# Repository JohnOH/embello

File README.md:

Embedded software from JeeLabs
==============================

Quick Links
-----------

* [Home page and docs](http://embello.jeelabs.org/)
* [Forth-based JeeLabs JeeNodes Zero](./explore/1608-forth)

Acknowledgments
---------------

With many thanks for the inspiring discussions and code contributions by:

* James Churchill
* Thorsten von Eicken
* Martyn Judd
* Matthias Koch
* Thomas Lohmüller
* John O'Hare
* Joris Pragt
* Frank (SevenW)
* Matthias Urlichs

-- [jcw](http://jeelabs.org/about/)

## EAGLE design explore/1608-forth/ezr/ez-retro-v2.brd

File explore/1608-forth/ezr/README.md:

## EZ-Retro v2

> For pinouts and code related to the hand-wired EZ-Retro v1, see [this
> snapshot](https://github.com/jeelabs/embello/tree/35cb87499ef61468ee42d1ae6326ffff1cd79f05/explore/1608-forth/ezr).

Pin connections:

    PB0 = eZ80 XIN, pin 86
    PB2 = eZ80 ZDA, pin 69 (w/ 10 kΩ pull-up)
    PB4 = eZ80 ZCL, pin 67 (w/ 10 kΩ pull-up)
    PB8 = eZ80 RESET, pin 55

Serial port:

    PA2 = eZ80 RX0, pin 74
    PA3 = eZ80 TX0, pin 73

External 2048 KB RAM:

    A0..A20 = eZ80 ADDR, pins 1-5/8-13/16-21/24-27
    D0..D7 = eZ80 DATA, pins 39-46
    CEN = eZ80 CS0, pin 33
    OEN = eZ80 RDN, pin 51
    WEN = eZ80 WRN, pin 52

Micro SD card:
 
    PA4 = µSD SSEL (CS)
    PA5 = µSD SCLK (CK)
    PA6 = µSD MISO (DO)
    PA7 = µSD MOSI (DI)

SPI interconnect, eZ80 is master:

    PB10 = eZ80 PB1,  pin 101 (BUSY: STM => eZ80)
    PB12 = eZ80 PB0,  pin 100 (NSS: eZ80 => STM))
           eZ80 SS,   pin 102 (10k pullup)
    PB13 = eZ80 SCK,  pin 103
    PB14 = eZ80 MISO, pin 106
    PB15 = eZ80 MOSI, pin 107

EZ-Retro v2 build, after the [PCB fixes](http://jeelabs.org/article/1717e):

Schematic of the STM32F103 board ([from eBay](http://www.ebay.com/itm/222253881878)):

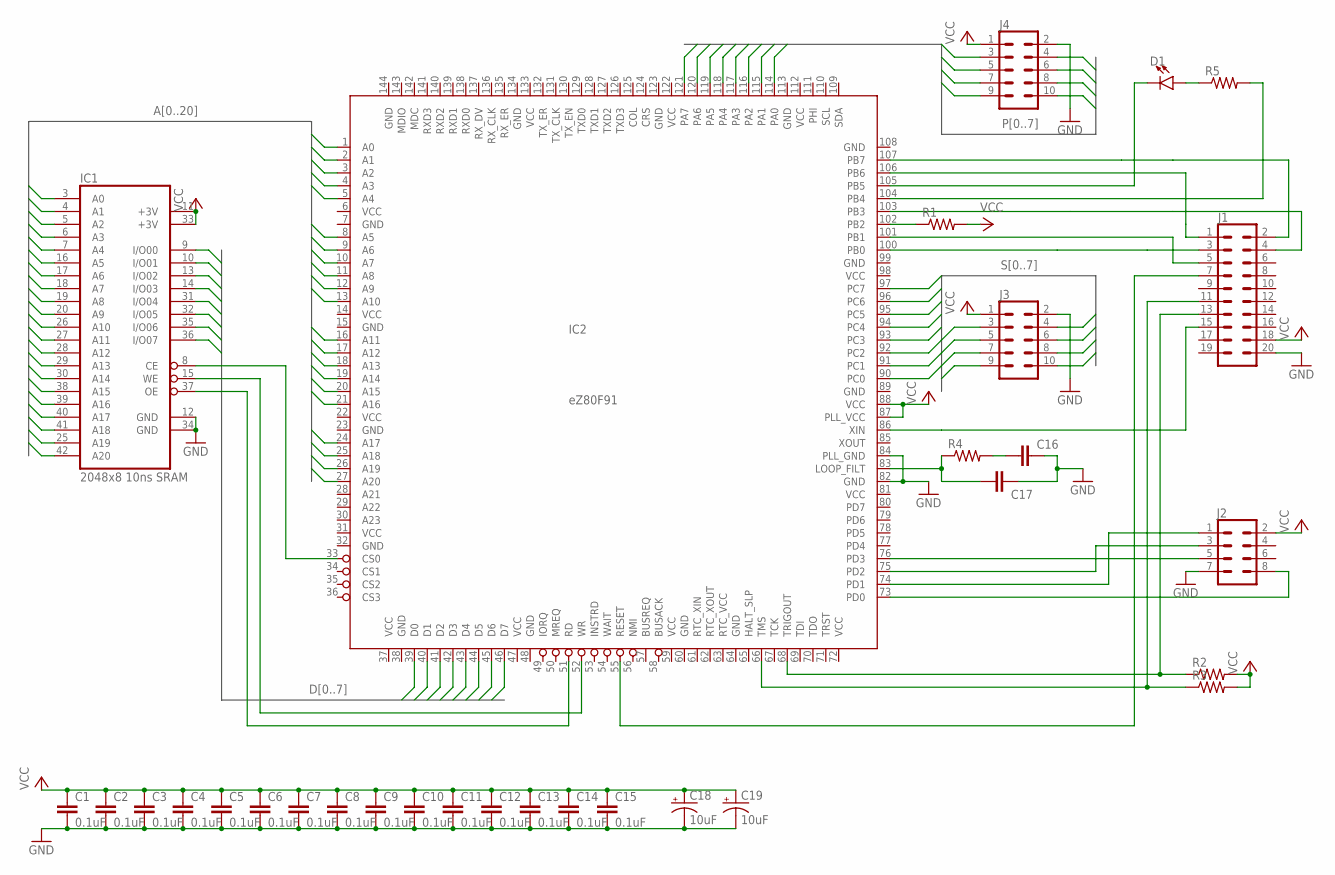
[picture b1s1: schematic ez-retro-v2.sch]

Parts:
C1, C2, C3, C4, C5, C6, C7, C8, C9, C10, C11, C12, C13, C14, C15, C16, C17: 0.1uF; 0603
C18, C19: 10uF; EIA3216
D1: LED1206; LED-1206
IC1: 2048x8 10ns SRAM; TSOPII-Z44
IC2: eZ80F91; TQFP144
J1: CONN_10X2NOSILK; 2X10_NOSILK
J2: CONN_04X2; 2X4
J3, J4: CONN_05X2NO_SILK; 2X5_NOSILK
R1, R2, R3, R4, R5: RESISTOR0603-RES; 0603-RES

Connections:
A0: IC1.3 (A0), IC2.1 (A0)
A1: IC1.4 (A1), IC2.2 (A1)
A2: IC1.5 (A2), IC2.3 (A2)
A3: IC1.6 (A3), IC2.4 (A3)
A4: IC1.7 (A4), IC2.5 (A4)
A5: IC1.16 (A5), IC2.8 (A5)
A6: IC1.17 (A6), IC2.9 (A6)
A7: IC1.18 (A7), IC2.10 (A7)
A8: IC1.19 (A8), IC2.11 (A8)
A9: IC1.20 (A9), IC2.12 (A9)
A10: IC1.26 (A10), IC2.13 (A10)
A11: IC1.27 (A11), IC2.16 (A11)
A12: IC1.28 (A12), IC2.17 (A12)
A13: IC1.29 (A13), IC2.18 (A13)
A14: IC1.30 (A14), IC2.19 (A14)
A15: IC1.38 (A15), IC2.20 (A15)
A16: IC1.39 (A16), IC2.21 (A16)
A17: IC1.40 (A17), IC2.24 (A17)
A18: IC1.41 (A18), IC2.25 (A18)
A19: IC1.25 (A19), IC2.26 (A19)
A20: IC1.42 (A20), IC2.27 (A20)
D0: IC1.9 (I/O00), IC2.39 (D0)
D1: IC1.10 (I/O01), IC2.40 (D1)
D2: IC1.13 (I/O02), IC2.41 (D2)
D3: IC1.14 (I/O03), IC2.42 (D3)
D4: IC1.31 (I/O04), IC2.43 (D4)
D5: IC1.32 (I/O05), IC2.44 (D5)
D6: IC1.35 (I/O06), IC2.45 (D6)
D7: IC1.36 (I/O07), IC2.46 (D7)
GND: C1.2, C2.2, C3.2, C4.2, C5.2, C6.2, C7.2, C8.2, C9.1, C10.2, C11.2, C12.2, C13.2, C14.2, C15.2, C16.2, C17.2, C18.-, C19.-, IC1.12 (GND), IC1.34 (GND), IC2.7 (GND), IC2.15 (GND), IC2.23 (GND), IC2.32 (GND), IC2.38 (GND), IC2.48 (GND), IC2.60 (GND), IC2.64 (GND), IC2.82 (GND), IC2.84 (PLL_GND), IC2.89 (GND), IC2.99 (GND), IC2.108 (GND), IC2.113 (GND), IC2.123 (GND), IC2.134 (GND), J1.20, J2.7, J3.2, J4.2
unnamed: IC1.37 (OE), IC2.51 (RD)
unnamed: IC1.15 (WE), IC2.52 (WR)
unnamed: IC1.8 (CE), IC2.33 (CS0)
unnamed: IC2.100 (PB0), J1.3
unnamed: IC2.106 (PB6), J1.1
unnamed: IC2.103 (PB3), J1.4
unnamed: IC2.107 (PB7), J1.2
unnamed: IC2.86 (XIN), J1.15
unnamed: IC2.55 (RESET), J1.7
unnamed: IC2.101 (PB1), J1.5
unnamed: IC2.66 (TMS), J1.11, R3.1
unnamed: IC2.102 (PB2), R1.1
unnamed: IC2.68 (TRIGOUT), J1.13, R2.1
unnamed: IC2.74 (PD1), J2.1
unnamed: IC2.73 (PD0), J2.8
unnamed: IC2.76 (PD3), J2.5
unnamed: IC2.75 (PD2), J2.3
unnamed: C17.1, IC2.83 (LOOP_FILT), R4.1
unnamed: C16.1, R4.2
unnamed: D1.A, R5.1
unnamed: D1.C, IC2.105 (PB5)
unnamed: IC2.104 (PB4), R5.2
P0: IC2.114 (PA0), J4.3
P1: IC2.115 (PA1), J4.4
P2: IC2.116 (PA2), J4.5
P3: IC2.117 (PA3), J4.6
P4: IC2.118 (PA4), J4.7
P5: IC2.119 (PA5), J4.8
P6: IC2.120 (PA6), J4.9
P7: IC2.121 (PA7), J4.10
RTC_VCC: IC2.63 (RTC_VCC)
S0: IC2.90 (PC0), J3.3
S1: IC2.91 (PC1), J3.4
S2: IC2.92 (PC2), J3.5
S3: IC2.93 (PC3), J3.6
S4: IC2.94 (PC4), J3.7
S5: IC2.95 (PC5), J3.8
S6: IC2.96 (PC6), J3.9
S7: IC2.97 (PC7), J3.10
VCC: C1.1, C2.1, C3.1, C4.1, C5.1, C6.1, C7.1, C8.1, C9.2, C10.1, C11.1, C12.1, C13.1, C14.1, C15.1, C18.+, C19.+, IC1.11 (+3V), IC1.33 (+3V), IC2.6 (VCC), IC2.14 (VCC), IC2.22 (VCC), IC2.31 (VCC), IC2.37 (VCC), IC2.47 (VCC), IC2.59 (VCC), IC2.72 (VCC), IC2.81 (VCC), IC2.87 (PLL_VCC), IC2.88 (VCC), IC2.98 (VCC), IC2.112 (VCC), IC2.122 (VCC), IC2.133 (VCC), J1.18, J2.2, J3.1, J4.1, R1.2, R2.2, R3.2
WP: IC2.144 (WP)

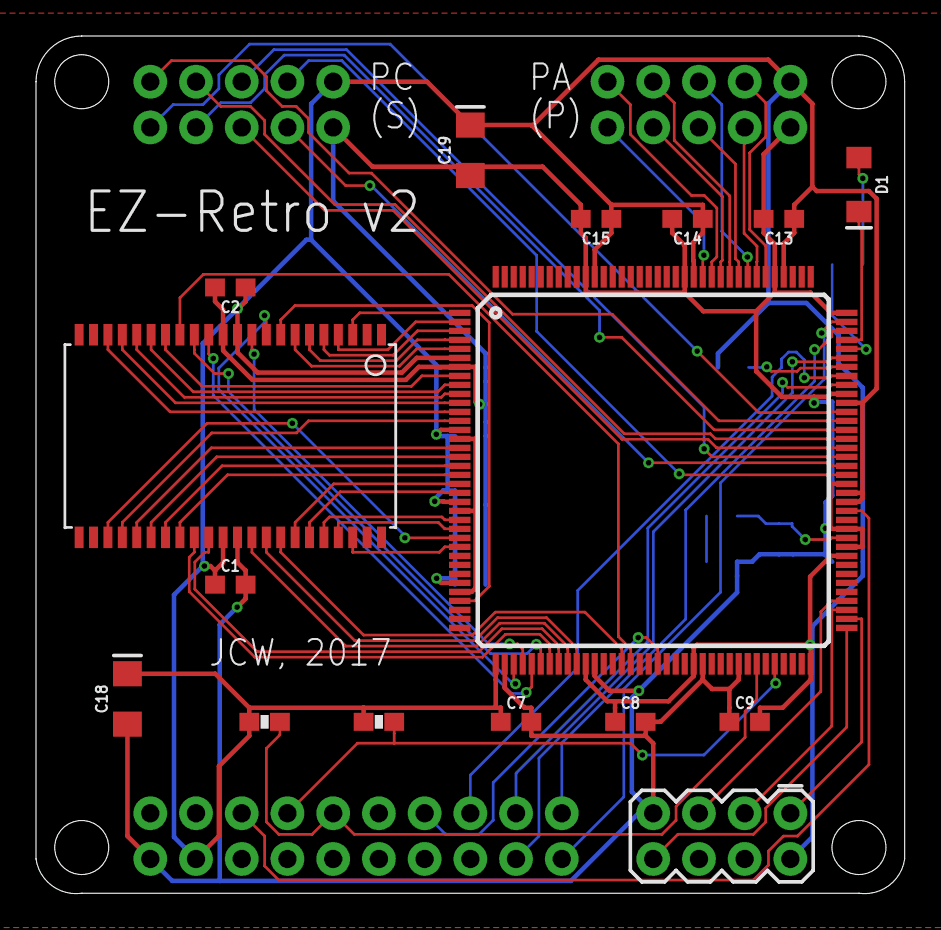
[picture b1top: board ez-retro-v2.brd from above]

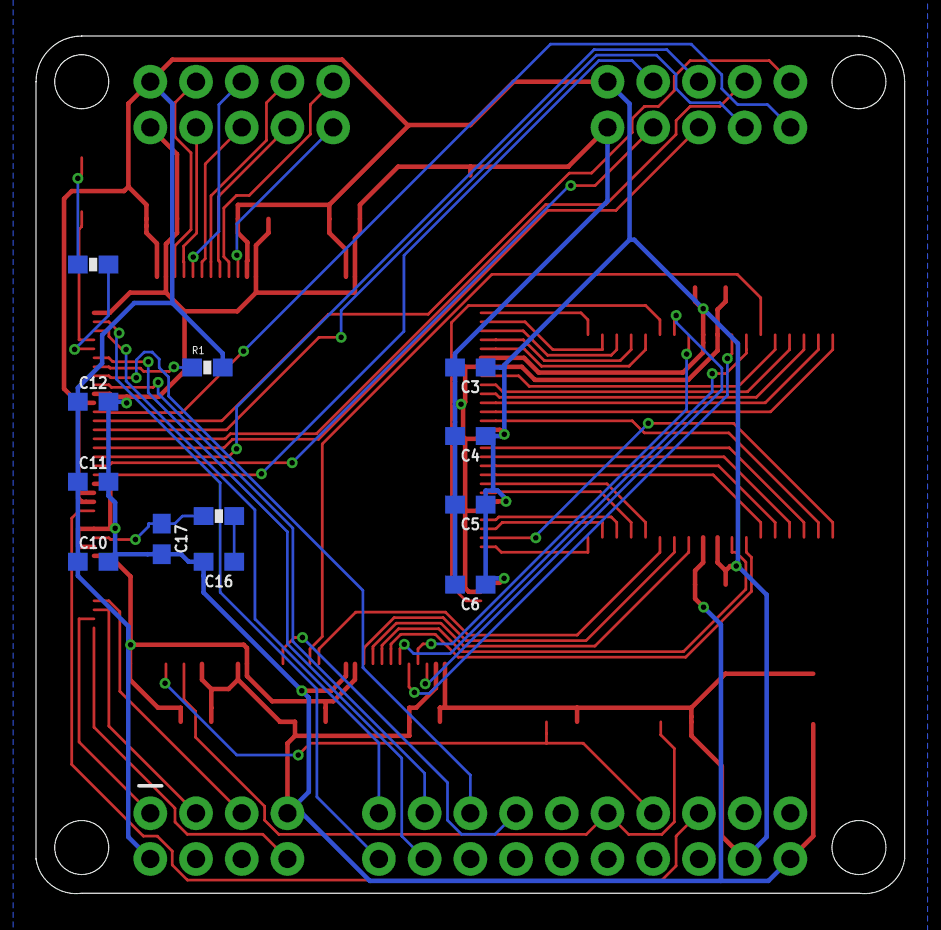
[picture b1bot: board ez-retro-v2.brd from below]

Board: 2 copper layers, 48.3 x 47.6 mm, 31 parts (12 on the bottom side), 69 nets.

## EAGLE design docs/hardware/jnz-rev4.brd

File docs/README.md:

This documentation can be viewed at <http://embello.jeelabs.org>.

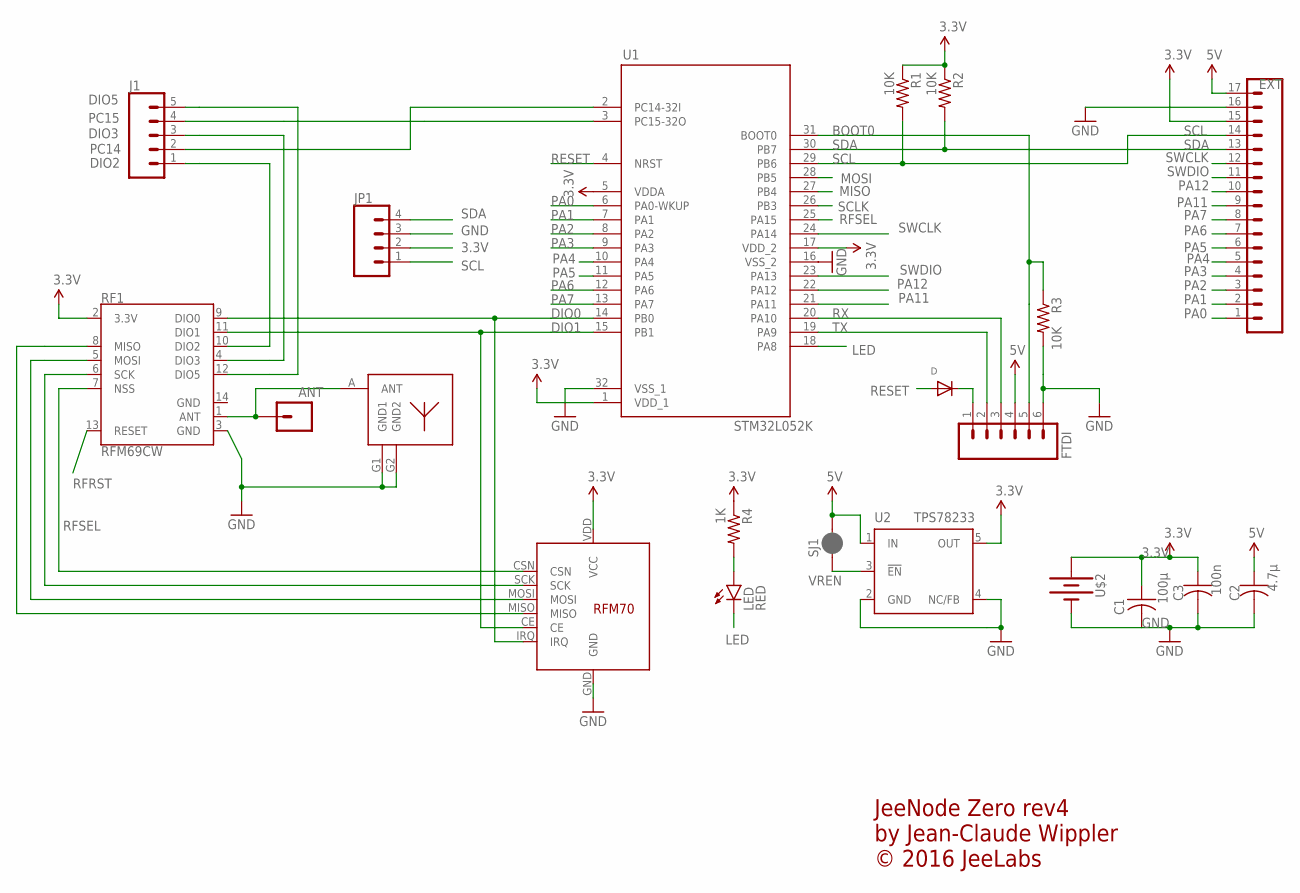
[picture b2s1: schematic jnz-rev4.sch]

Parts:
ANT: CONN_01PTH_NO_SILK_KIT; 1X01NS_KIT
C1: 100µ; C1206
C2: 4.7µ; C0805
C3: 100n; C0603
D: DIODESOD-323F; SOD-323F
EXT: CONN_17NOSILK; 1X17_NO_SILK
FTDI: CONN_06NO_SILK_FEMALE_PTH; 1X06_NO_SILK
J1: CONN_05NO_SILK; 1X05_NO_SILK
JP1: CONN_04SMD_RA_FEMALE; 1X04_SMD_RA_FEMALE
LED: RED; LED-0603
R1, R2, R3: 10K; R0603
R4: 1K; R0603
RF1: RFM69CW; RFM69CW-XXXS2
RF2: RFM75; RFM70
SJ1: JUMPER-SMT_2_NC_PASTE_NO-SILK; SMT-JUMPER_2_NC_PASTE_NO-SILK
U1: STM32L052K; TQFP32-08
U2: TPS78233; SOT23-DBV
U$1: UFL
U$2: BATTERY-20MM_SMD_4LEGS; BATTCON_20MM_4LEGS

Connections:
3.3V: C1.1, C3.1, EXT.15, JP1.2, R1.1, R2.1, R4.1, RF1.2 (3.3V), RF2.VDD (VCC), U1.1 (VDD_1), U1.5 (VDDA), U1.17 (VDD_2), U2.5 (OUT), U$2.POSITIVE@1 (+), U$2.POSITIVE@2 (+), U$2.POSITIVE@3 (+), U$2.POSITIVE@4 (+)
5V: C2.1, EXT.17, FTDI.4, SJ1.2, U2.1 (IN)
BOOT0: FTDI.5, R3.1, U1.31 (BOOT0)
DIO0: RF1.9 (DIO0), RF2.IRQ, U1.14 (PB0)
DIO1: RF1.11 (DIO1), RF2.CE, U1.15 (PB1)
DIO2: J1.1, RF1.10 (DIO2)
DIO3: J1.3, RF1.4 (DIO3)
DIO5: J1.5, RF1.12 (DIO5)
GND: C1.2, C2.2, C3.2, EXT.16, FTDI.6, JP1.3, R3.2, RF1.3 (GND), RF1.14 (GND), RF2.GND, U1.16 (VSS_2), U1.32 (VSS_1), U2.2 (GND), U2.4 (NC/FB), U$1.G1 (GND1), U$1.G2 (GND2), U$2.NEGATIVE (-)
LED: LED.C, U1.18 (PA8)
MISO: RF1.8 (MISO), RF2.MISO, U1.27 (PB4)
MOSI: RF1.5 (MOSI), RF2.MOSI, U1.28 (PB5)
unnamed: D.C, FTDI.1
unnamed: LED.A, R4.2
unnamed: ANT.1, RF1.1 (ANT), U$1.A (ANT)
PA0: EXT.1, U1.6 (PA0-WKUP)
PA1: EXT.2, U1.7 (PA1)
PA2: EXT.3, U1.8 (PA2)
PA3: EXT.4, U1.9 (PA3)
PA4: EXT.5, U1.10 (PA4)
PA5: EXT.6, U1.11 (PA5)
PA6: EXT.7, U1.12 (PA6)
PA7: EXT.8, U1.13 (PA7)
PA11: EXT.9, U1.21 (PA11)
PA12: EXT.10, U1.22 (PA12)
PC14: J1.2, U1.2 (PC14-32I)
PC15: J1.4, U1.3 (PC15-32O)
RESET: D.A, U1.4 (NRST)
RFRST: RF1.13 (RESET)
RFSEL: RF1.7 (NSS), RF2.CSN, U1.25 (PA15)
RX: FTDI.3, U1.20 (PA10)
SCL: EXT.14, JP1.1, R1.2, U1.29 (PB6)
SCLK: RF1.6 (SCK), RF2.SCK, U1.26 (PB3)
SDA: EXT.13, JP1.4, R2.2, U1.30 (PB7)
SWCLK: EXT.12, U1.24 (PA14)
SWDIO: EXT.11, U1.23 (PA13)
TX: FTDI.2, U1.19 (PA9)
VREN: SJ1.1, U2.3 (!EN)

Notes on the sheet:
JeeNode Zero rev4 by Jean-Claude Wippler © 2016 JeeLabs

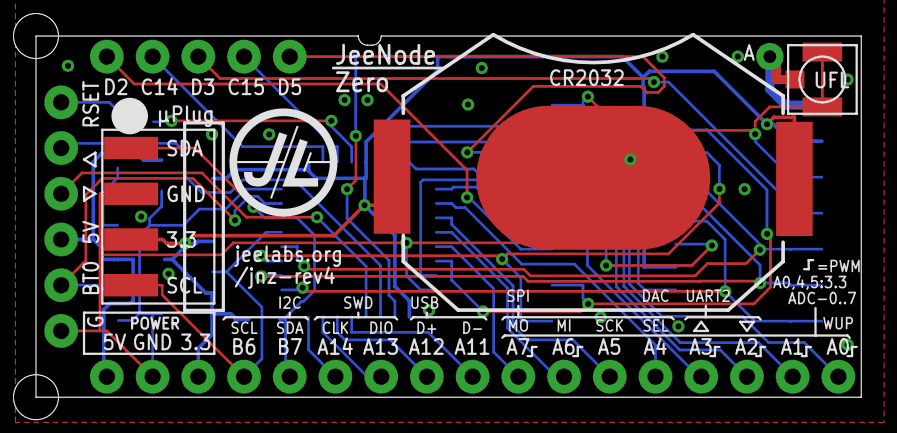
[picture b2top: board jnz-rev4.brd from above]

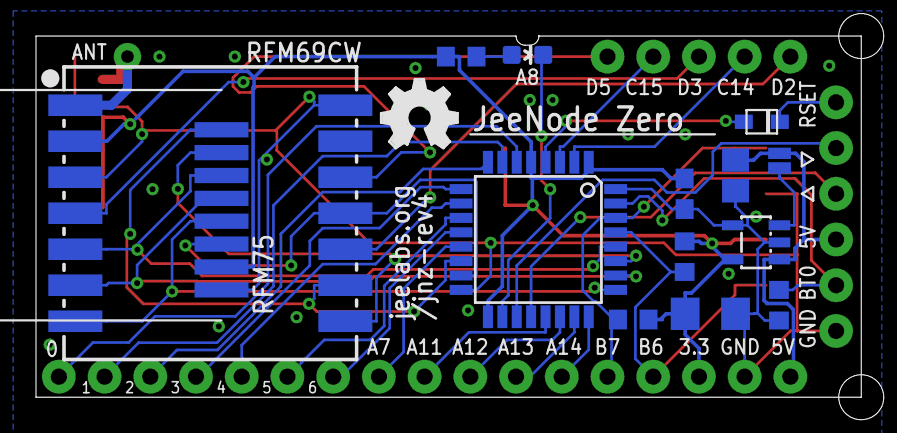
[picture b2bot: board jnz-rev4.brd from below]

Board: 2 copper layers, 45.8 x 20.1 mm, 22 parts (15 on the bottom side), 37 nets.

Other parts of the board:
LOGO1: OSHW_LOGO_FILLX0150-NT; OSHW_FILLX150_NOTEXT

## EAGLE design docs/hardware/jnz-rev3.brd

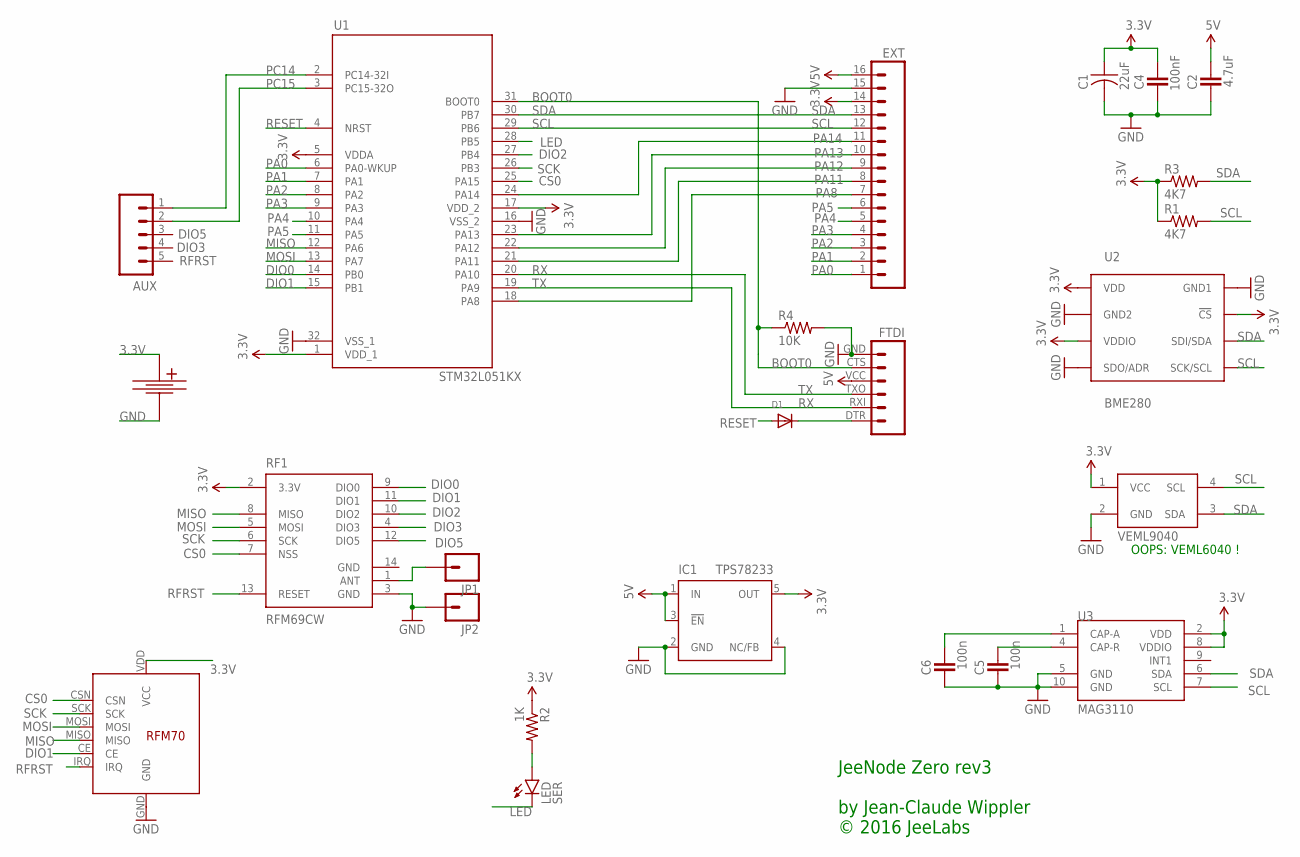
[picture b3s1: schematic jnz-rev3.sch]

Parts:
AUX: M05NO_SILK; 1X05_NO_SILK
C1: 22uF; C0805
C2: 4.7uF; C0805K
C4: 100nF; C0603K
C5, C6: 100n; C0603K
D1: DIODESOD-323F; SOD-323F
EXT: M161X16_NO_SILK; 1X16_NO_SILK
FTDI: FTDI_BASICPTH; FTDI_BASIC
IC1: TPS78233; SOT23-DBV
JP1, JP2: M01NOSILK-KIT; 1X01NS-KIT
LED: SER; LED-0603
R1, R3: 4K7; 0603-RES
R2: 1K; 0603-RES
R4: 10K; 0603-RES
RF1: RFM69CW; RFM69CW-XXXS2
RF2: RFM7x; RFM70
U1: STM32L051KX; TQFP32-08
U2: BME280; BME280_LGA
U3: MAG3110; DFN-10
U$2: CR2032-SMD
U$3: VEML6040; OPLGA-4

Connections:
3.3V: C1.1, C4.1, EXT.14, IC1.5 (OUT), R1.1, R2.1, R3.1, RF1.2 (3.3V), RF2.VDD (VCC), U1.1 (VDD_1), U1.5 (VDDA), U1.17 (VDD_2), U2.P$2 (!CS), U2.P$6 (VDDIO), U2.P$8 (VDD), U3.2 (VDD), U3.8 (VDDIO), U$2.POS (+), U$3.1 (VCC)
5V: C2.1, EXT.16, FTDI.VCC (4), IC1.1 (IN), IC1.3 (!EN)
BOOT0: FTDI.CTS (5), R4.1, U1.31 (BOOT0)
CS0: RF1.7 (NSS), RF2.CSN, U1.25 (PA15)
DIO0: RF1.9 (DIO0), U1.14 (PB0)
DIO1: RF1.11 (DIO1), RF2.CE, U1.15 (PB1)
DIO2: RF1.10 (DIO2), U1.27 (PB4)
DIO3: AUX.4, RF1.4 (DIO3)
DIO5: AUX.3, RF1.12 (DIO5)
GND: C1.2, C2.2, C4.2, C5.2, C6.2, EXT.15, FTDI.GND (6), IC1.2 (GND), IC1.4 (NC/FB), JP2.1, R4.2, RF1.3 (GND), RF1.14 (GND), RF2.GND, U1.16 (VSS_2), U1.32 (VSS_1), U2.P$1 (GND1), U2.P$5 (SDO/ADR), U2.P$7 (GND2), U3.5 (GND), U3.10 (GND), U$2.NEG (-), U$3.2 (GND)
LED: LED.C, U1.28 (PB5)
MISO: RF1.8 (MISO), RF2.MISO, U1.12 (PA6)
MOSI: RF1.5 (MOSI), RF2.MOSI, U1.13 (PA7)
unnamed: D1.C, FTDI.DTR (1)
unnamed: LED.A, R2.2
unnamed: C5.1, U3.4 (CAP-R)
unnamed: C6.1, U3.1 (CAP-A)
unnamed: JP1.1, RF1.1 (ANT)
PA0: EXT.1, U1.6 (PA0-WKUP)
PA1: EXT.2, U1.7 (PA1)
PA2: EXT.3, U1.8 (PA2)
PA3: EXT.4, U1.9 (PA3)
PA4: EXT.5, U1.10 (PA4)
PA5: EXT.6, U1.11 (PA5)
PA8: EXT.7, U1.18 (PA8)
PA11: EXT.8, U1.21 (PA11)
PA12: EXT.9, U1.22 (PA12)
PA13: EXT.10, U1.23 (PA13)
PA14: EXT.11, U1.24 (PA14)
PC14: AUX.1, U1.2 (PC14-32I)
PC15: AUX.2, U1.3 (PC15-32O)
RESET: D1.A, U1.4 (NRST)
RFRST: AUX.5, RF1.13 (RESET), RF2.IRQ
RX: FTDI.TXO (3), U1.20 (PA10)
SCK: RF1.6 (SCK), RF2.SCK, U1.26 (PB3)
SCL: EXT.12, R1.2, U1.29 (PB6), U2.P$4 (SCK/SCL), U3.7 (SCL), U$3.4 (SCL)
SDA: EXT.13, R3.2, U1.30 (PB7), U2.P$3 (SDI/SDA), U3.6 (SDA), U$3.3 (SDA)
TX: FTDI.RXI (2), U1.19 (PA9)

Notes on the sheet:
JeeNode Zero rev3 by Jean-Claude Wippler © 2016 JeeLabs
OOPS: VEML6040 !

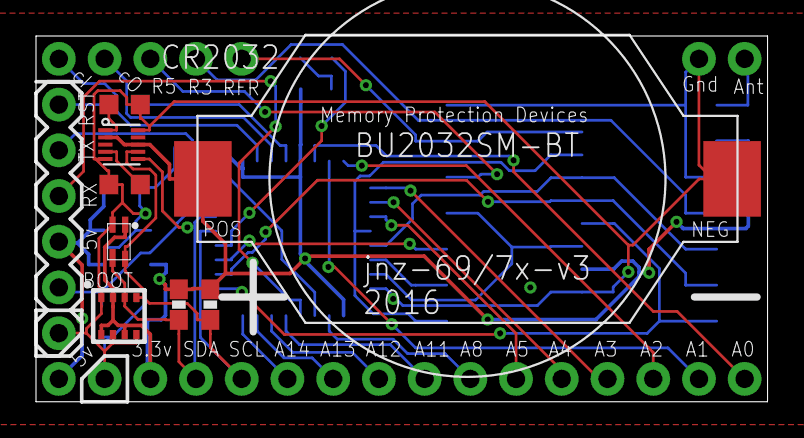
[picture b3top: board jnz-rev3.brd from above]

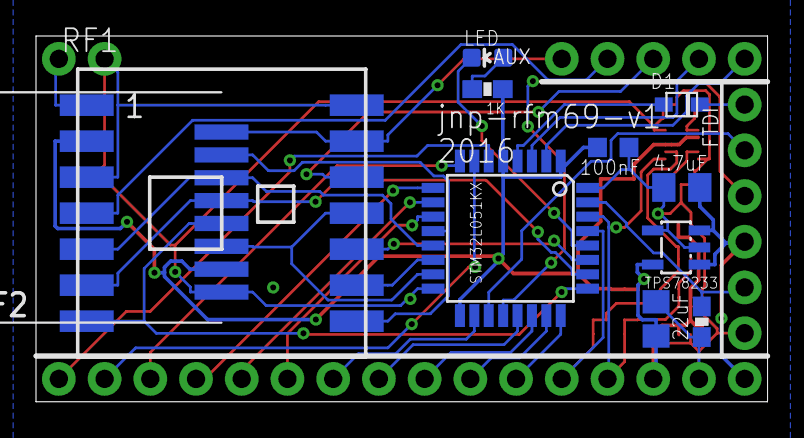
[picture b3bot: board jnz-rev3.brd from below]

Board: 2 copper layers, 40.6 x 20.3 mm, 24 parts (11 on the bottom side), 38 nets.

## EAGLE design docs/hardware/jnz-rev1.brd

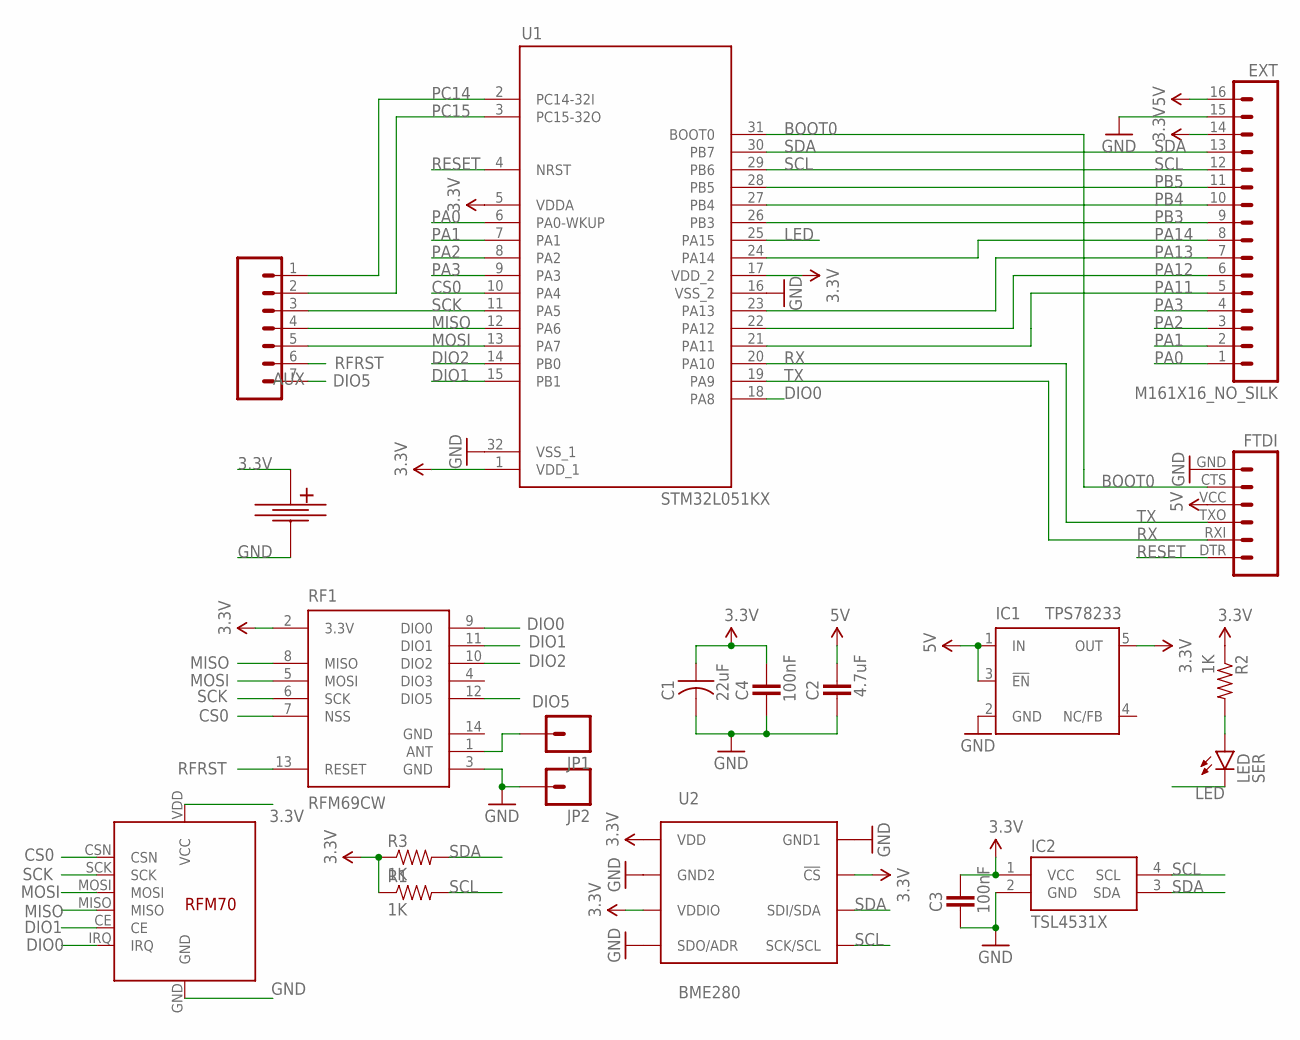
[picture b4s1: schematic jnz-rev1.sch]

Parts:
AUX: M07; 1X07
C1: 22uF; C0805
C2: 4.7uF; C0805K
C3, C4: 100nF; C0603K
EXT: M161X16_NO_SILK; 1X16_NO_SILK
FTDI: FTDI_BASICPTH; FTDI_BASIC
IC1: TPS78233; SOT23-DBV
IC2: TSL4531X; AMS_CL
JP1, JP2: M01NOSILK-KIT; 1X01NS-KIT
LED: SER; LED-0603
R1, R2, R3: 1K; 0603-RES
RF1: RFM69CW; RFM69CW-XXXS2
RF2: RFM7x; RFM70
U1: STM32L051KX; TQFP32-08
U2: BME280; BME280_LGA
U$2: CR2032-SMD

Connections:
3.3V: C1.1, C3.1, C4.1, EXT.14, IC1.5 (OUT), IC2.1 (VCC), R1.1, R2.1, R3.1, RF1.2 (3.3V), RF2.VDD (VCC), U1.1 (VDD_1), U1.5 (VDDA), U1.17 (VDD_2), U2.P$2 (!CS), U2.P$6 (VDDIO), U2.P$8 (VDD), U$2.POS (+)
5V: C2.1, EXT.16, FTDI.VCC (4), IC1.1 (IN), IC1.3 (!EN)
BOOT0: FTDI.CTS (5), U1.31 (BOOT0)
CS0: RF1.7 (NSS), RF2.CSN, U1.10 (PA4)
DIO0: RF1.9 (DIO0), RF2.IRQ, U1.18 (PA8)
DIO1: RF1.11 (DIO1), RF2.CE, U1.15 (PB1)
DIO2: RF1.10 (DIO2), U1.14 (PB0)
DIO5: AUX.7, RF1.12 (DIO5)
GND: C1.2, C2.2, C3.2, C4.2, EXT.15, FTDI.GND (6), IC1.2 (GND), IC2.2 (GND), JP2.1, RF1.3 (GND), RF1.14 (GND), RF2.GND, U1.16 (VSS_2), U1.32 (VSS_1), U2.P$1 (GND1), U2.P$5 (SDO/ADR), U2.P$7 (GND2), U$2.NEG (-)
LED: LED.C, U1.25 (PA15)
MISO: AUX.4, RF1.8 (MISO), RF2.MISO, U1.12 (PA6)
MOSI: AUX.5, RF1.5 (MOSI), RF2.MOSI, U1.13 (PA7)
unnamed: LED.A, R2.2
unnamed: JP1.1, RF1.1 (ANT)
PA0: EXT.1, U1.6 (PA0-WKUP)
PA1: EXT.2, U1.7 (PA1)
PA2: EXT.3, U1.8 (PA2)
PA3: EXT.4, U1.9 (PA3)
PA11: EXT.5, U1.21 (PA11)
PA12: EXT.6, U1.22 (PA12)
PA13: EXT.7, U1.23 (PA13)
PA14: EXT.8, U1.24 (PA14)
PB3: EXT.9, U1.26 (PB3)
PB4: EXT.10, U1.27 (PB4)
PB5: EXT.11, U1.28 (PB5)
PC14: AUX.1, U1.2 (PC14-32I)
PC15: AUX.2, U1.3 (PC15-32O)
RESET: FTDI.DTR (1), U1.4 (NRST)
RFRST: AUX.6, RF1.13 (RESET)
RX: FTDI.TXO (3), U1.20 (PA10)
SCK: AUX.3, RF1.6 (SCK), RF2.SCK, U1.11 (PA5)
SCL: EXT.12, IC2.4 (SCL), R1.2, U1.29 (PB6), U2.P$4 (SCK/SCL)
SDA: EXT.13, IC2.3 (SDA), R3.2, U1.30 (PB7), U2.P$3 (SDI/SDA)
TX: FTDI.RXI (2), U1.19 (PA9)

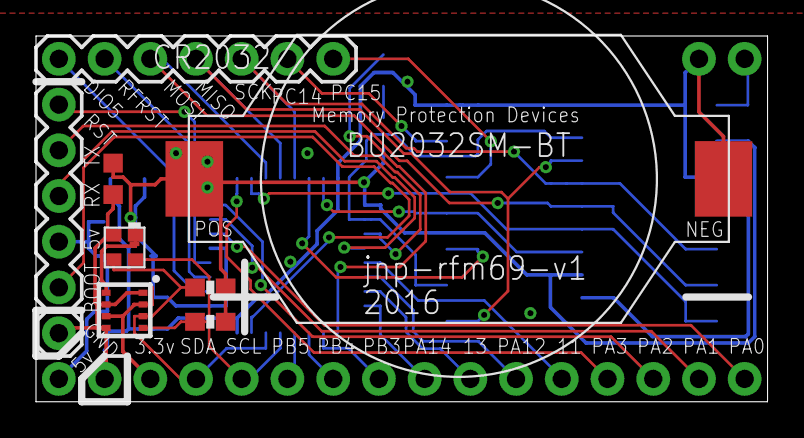
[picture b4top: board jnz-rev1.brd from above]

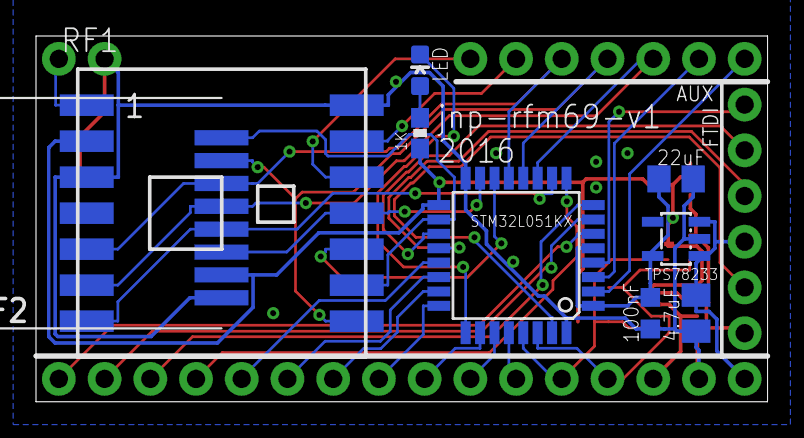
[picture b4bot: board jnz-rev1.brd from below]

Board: 2 copper layers, 40.6 x 20.3 mm, 20 parts (9 on the bottom side), 34 nets.

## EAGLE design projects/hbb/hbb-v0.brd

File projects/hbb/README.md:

See <http://jeelabs.org/2016/01/arduino-shields...-or-not/>

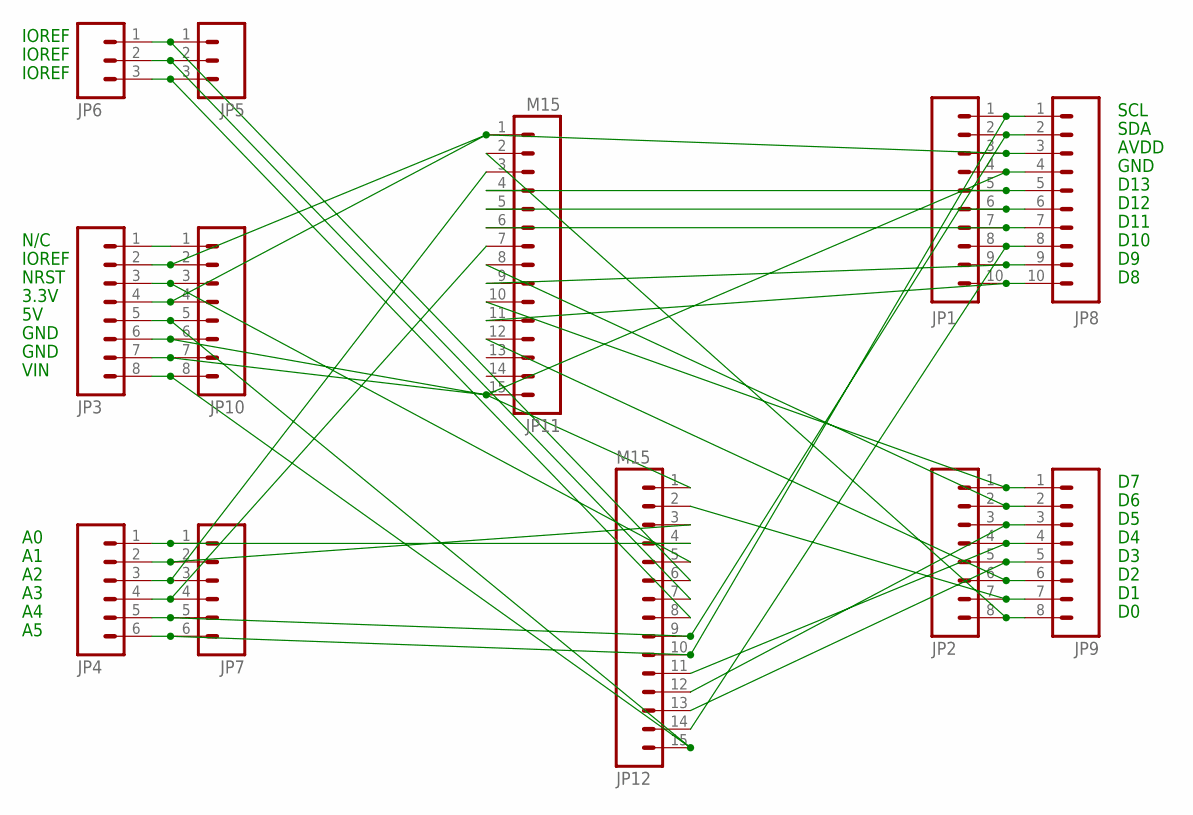
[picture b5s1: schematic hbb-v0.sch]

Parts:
JP1, JP8: M10NO_SILK_PTH_FEMALE; 1X10_NO_SILK
JP2, JP3, JP9, JP10: M08NO_SILK_FEMALE_PTH; 1X08_NO_SILK
JP4, JP7: M06NO_SILK_FEMALE_PTH; 1X06_NO_SILK
JP5: M03LOCK_NO_SILK; 1X03_LOCK_NO_SILK
JP6: M03PTH; 1X03
JP11, JP12: M15; 1X15

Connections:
GND: JP1.4, JP3.6, JP3.7, JP8.4, JP10.6, JP10.7, JP11.15, JP12.1
unnamed: JP5.1, JP6.1, JP12.6
unnamed: JP5.2, JP6.2, JP12.7
unnamed: JP5.3, JP6.3, JP12.8
unnamed: JP4.1, JP7.1, JP12.4
unnamed: JP4.2, JP7.2, JP12.3
unnamed: JP4.3, JP7.3, JP11.3
unnamed: JP4.4, JP7.4, JP11.7
unnamed: JP1.2, JP4.5, JP7.5, JP8.2, JP12.9
unnamed: JP1.1, JP4.6, JP7.6, JP8.1, JP12.10
unnamed: JP1.5, JP8.5, JP11.4
unnamed: JP1.6, JP8.6, JP11.5
unnamed: JP1.7, JP8.7, JP11.6
unnamed: JP1.8, JP8.8, JP12.14
unnamed: JP1.9, JP8.9, JP11.9
unnamed: JP1.10, JP8.10, JP11.11
unnamed: JP2.1, JP9.1, JP11.10
unnamed: JP2.2, JP9.2, JP11.8
unnamed: JP2.3, JP9.3, JP12.12
unnamed: JP2.4, JP9.4, JP12.11
unnamed: JP2.5, JP9.5, JP12.13
unnamed: JP2.6, JP9.6, JP11.12
unnamed: JP2.7, JP9.7, JP12.2
unnamed: JP2.8, JP9.8, JP11.2
unnamed: JP3.1, JP10.1
unnamed: JP1.3, JP3.2, JP3.4, JP8.3, JP10.2, JP10.4, JP11.1
unnamed: JP3.3, JP10.3, JP12.5
unnamed: JP3.5, JP3.8, JP10.5, JP10.8, JP12.15

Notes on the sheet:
N/C
IOREF
NRST
3.3V
GND
VIN
SCL
SDA
AVDD
D13
D12
D11
D10

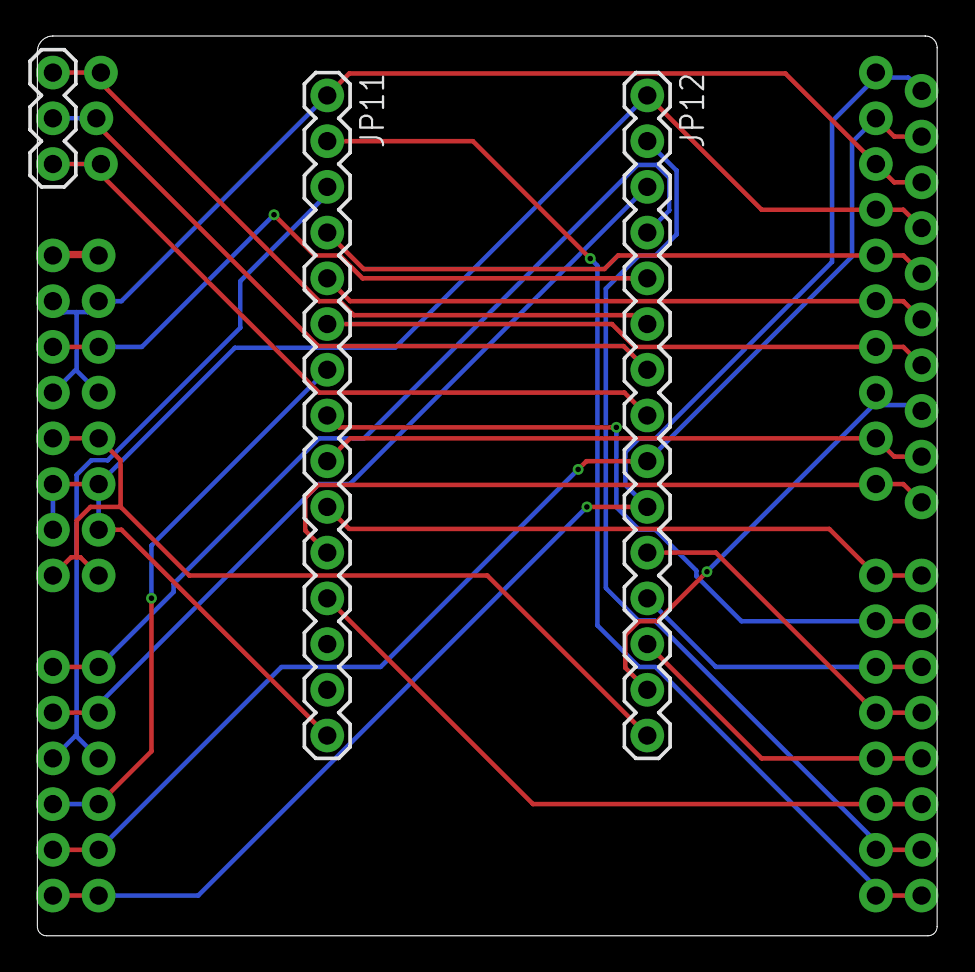
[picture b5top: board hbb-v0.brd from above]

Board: 2 copper layers, 50.0 x 50.0 mm, 12 parts (0 on the bottom side), 28 nets.

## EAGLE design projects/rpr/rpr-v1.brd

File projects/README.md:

In this folder:

**Arduino Sketch Collection** - <http://jeelabs.org/ask>

**Garage Parking Aid** - <http://jeelabs.org/gpa>

**Hy-Tiny Base Board** - <http://jeelabs.org/hbb>

**Micro Power Snitch** - <http://jeelabs.org/mps>

**RF Node Watcher** - <http://jeelabs.org/rnw>

**RasPi RF** - <http://jeelabs.org/rpr>

**Tinker Pico** - <http://jeelabs.org/tkp>

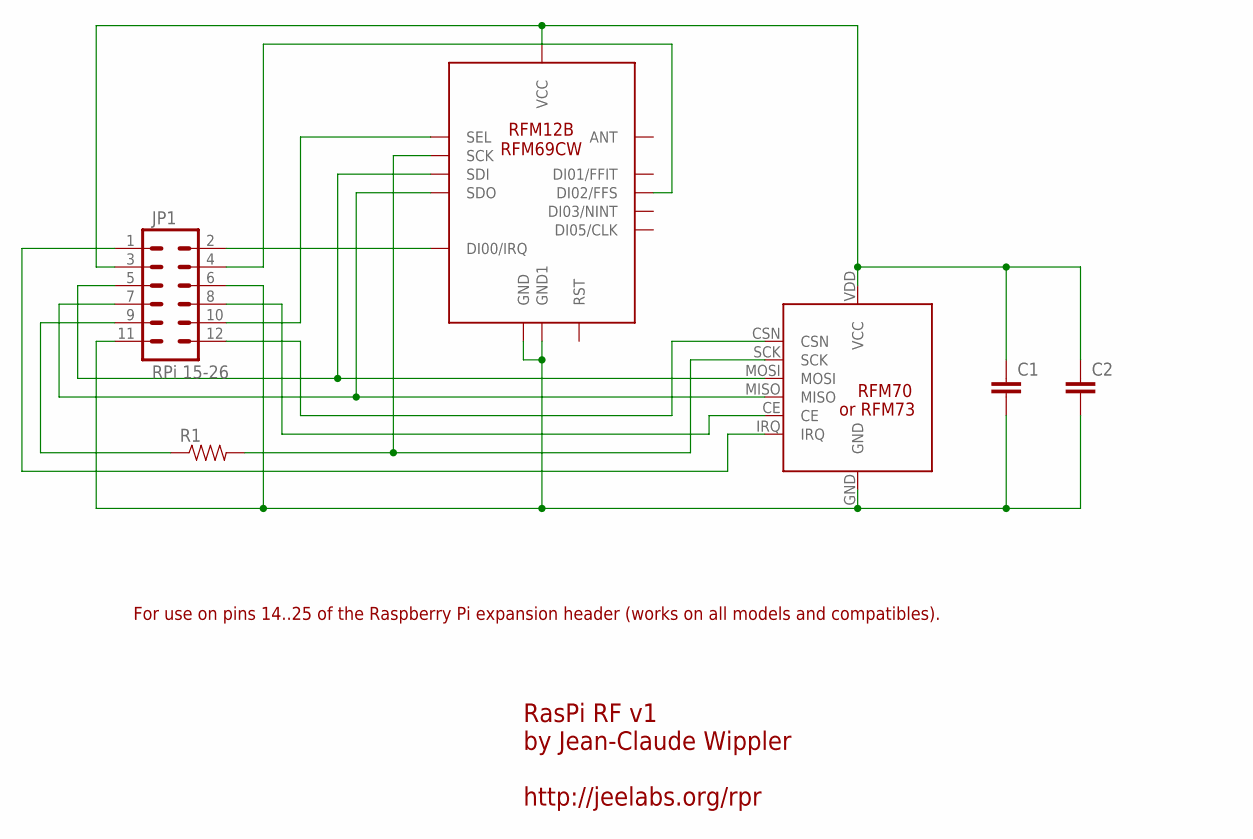
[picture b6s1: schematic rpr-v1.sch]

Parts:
C1, C2: CAP0805; 0805
JP1: RPi 15-26; 2X6
R1: RESISTOR0603-RES; 0603-RES
RFM12B/69CW: RFM12B/69CW
U$1: RFM70

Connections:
GND: C1.2, C2.2, JP1.6, JP1.11, RFM12B/69CW.GND, RFM12B/69CW.GND1, U$1.GND
unnamed: C1.1, C2.1, JP1.3, RFM12B/69CW.VDD (VCC), U$1.VDD (VCC)
unnamed: JP1.12, U$1.CSN
unnamed: JP1.10, RFM12B/69CW.SEL
unnamed: JP1.5, RFM12B/69CW.SDI, U$1.MOSI
unnamed: JP1.7, RFM12B/69CW.SDO, U$1.MISO
unnamed: JP1.9, R1.1
unnamed: R1.2, RFM12B/69CW.SCK, U$1.SCK
unnamed: JP1.8, U$1.CE
unnamed: JP1.1, U$1.IRQ
unnamed: JP1.2, RFM12B/69CW.IRQ (DI00/IRQ)
unnamed: JP1.4, RFM12B/69CW.FFS (DI02/FFS)

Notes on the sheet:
RasPi RF v1 by Jean-Claude Wippler http://jeelabs.org/rpr
For use on pins 14..25 of the Raspberry Pi expansion header (works on all models and compatibles).
or RFM73

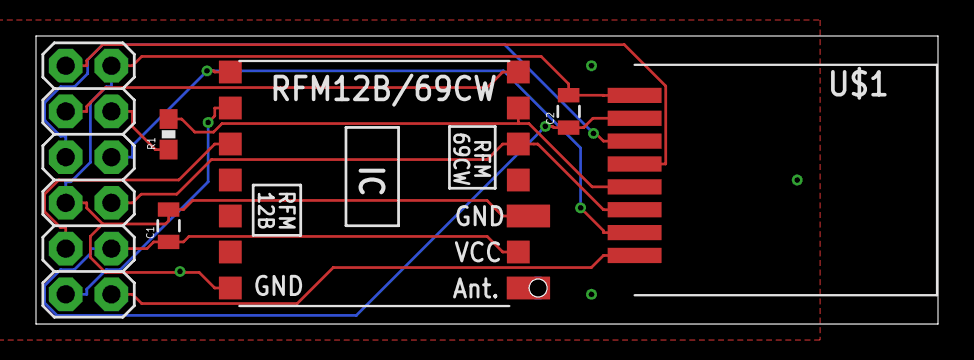
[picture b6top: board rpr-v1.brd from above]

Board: 2 copper layers, 50.1 x 16.0 mm, 6 parts (0 on the bottom side), 12 nets.

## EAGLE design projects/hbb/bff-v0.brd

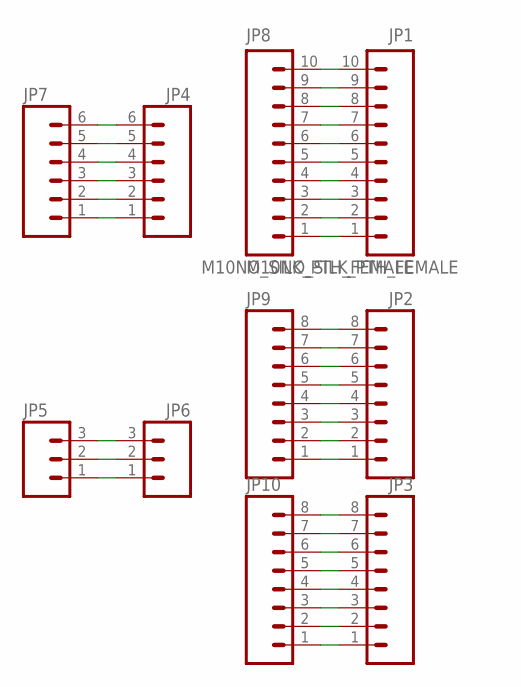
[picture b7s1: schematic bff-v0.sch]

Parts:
JP1, JP8: M10NO_SILK_PTH_FEMALE; 1X10_NO_SILK
JP2, JP3, JP9, JP10: M08NO_SILK_FEMALE_PTH; 1X08_NO_SILK
JP4, JP7: M06NO_SILK_FEMALE_PTH; 1X06_NO_SILK
JP5: M03LOCK_NO_SILK; 1X03_LOCK_NO_SILK
JP6: M03PTH; 1X03

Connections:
unnamed: JP5.1, JP6.1
unnamed: JP5.2, JP6.2
unnamed: JP5.3, JP6.3
unnamed: JP4.1, JP7.1
unnamed: JP4.2, JP7.2
unnamed: JP4.3, JP7.3
unnamed: JP4.4, JP7.4
unnamed: JP4.5, JP7.5
unnamed: JP4.6, JP7.6
unnamed: JP1.1, JP8.1
unnamed: JP1.2, JP8.2
unnamed: JP1.3, JP8.3
unnamed: JP1.4, JP8.4
unnamed: JP1.5, JP8.5
unnamed: JP1.6, JP8.6
unnamed: JP1.7, JP8.7
unnamed: JP1.8, JP8.8
unnamed: JP1.9, JP8.9
unnamed: JP1.10, JP8.10
unnamed: JP2.1, JP9.1
unnamed: JP2.2, JP9.2
unnamed: JP2.3, JP9.3
unnamed: JP2.4, JP9.4
unnamed: JP2.5, JP9.5
unnamed: JP2.6, JP9.6
unnamed: JP2.7, JP9.7
unnamed: JP2.8, JP9.8
unnamed: JP3.1, JP10.1
unnamed: JP3.2, JP10.2
unnamed: JP3.3, JP10.3
unnamed: JP3.4, JP10.4
unnamed: JP3.5, JP10.5
unnamed: JP3.6, JP10.6
unnamed: JP3.7, JP10.7
unnamed: JP3.8, JP10.8

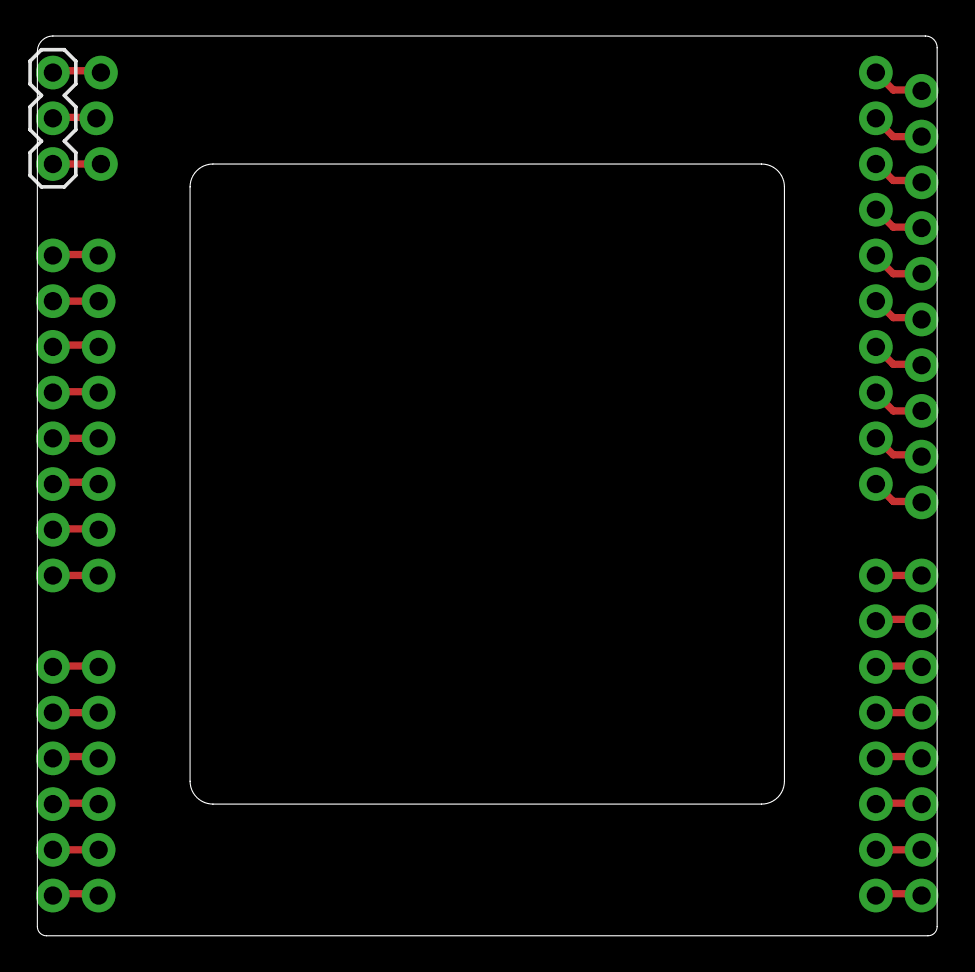
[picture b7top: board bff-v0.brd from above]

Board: 2 copper layers, 50.0 x 50.0 mm, 10 parts (0 on the bottom side), 35 nets.

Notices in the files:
parts and their libraries:
SparkFun-Connectors: Licensing: Creative Commons ShareAlike 4.0 International - https://creativecommons.org/licenses/by-sa/4.0
